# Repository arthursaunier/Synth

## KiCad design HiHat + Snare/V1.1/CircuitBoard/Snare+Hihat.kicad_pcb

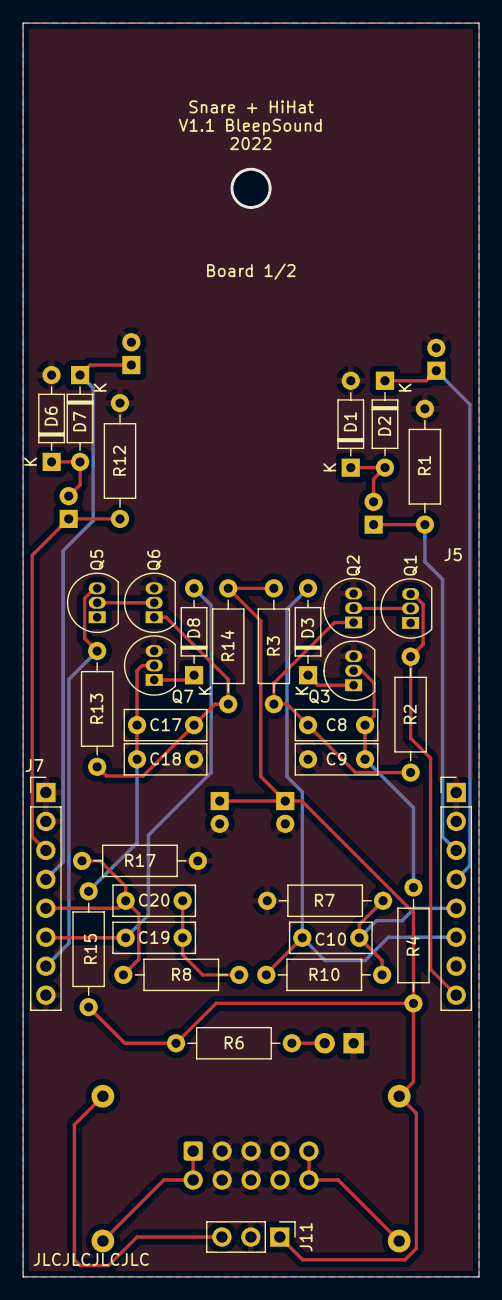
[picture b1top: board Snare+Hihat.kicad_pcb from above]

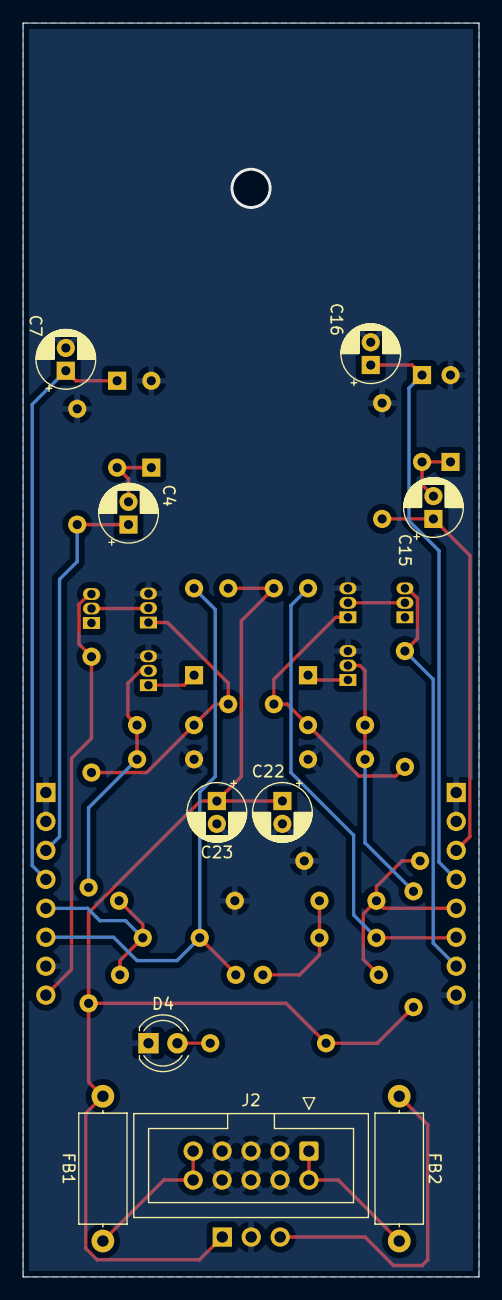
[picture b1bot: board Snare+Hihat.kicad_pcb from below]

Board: 2 copper layers, 40.0 x 110.0 mm, 45 parts (10 on the bottom side), 27 nets.

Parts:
C4, C7, C15, C16: 10µF; CP_Radial_D5.0mm_P2.00mm
C8, C17: 1µF; C_Disc_D7.0mm_W2.5mm_P5.00mm
C9: 0.1µF; C_Disc_D7.0mm_W2.5mm_P5.00mm
C10, C20: .1µF; C_Disc_D7.0mm_W2.5mm_P5.00mm
C18: 10nF; C_Disc_D7.0mm_W2.5mm_P5.00mm
C19: 680pF; C_Disc_D7.0mm_W2.5mm_P5.00mm
C22, C23: 100µ; CP_Radial_D5.0mm_P2.00mm
D1, D2, D3, D6, D7, D8: 1N4148; D_DO-35_SOD27_P7.62mm_Horizontal
D4: LED-12V; LED_D4.0mm
FB1, FB2: 10R; L_Axial_L9.5mm_D4.0mm_P12.70mm_Horizontal_Fastron_SMCC
J2: Power Input; IDC-Header_2x05_P2.54mm_Vertical
J5, J7: Conn_01x08_Male; PinHeader_1x08_P2.54mm_Vertical
J11: Conn_01x03_Male; PinHeader_1x03_P2.54mm_Vertical
Q1, Q2, Q3, Q5, Q6, Q7: BC546; TO-92_Inline
R1, R3, R12, R14: 4k7; R_Axial_DIN0207_L6.3mm_D2.5mm_P10.16mm_Horizontal
R2, R13: 47k; R_Axial_DIN0207_L6.3mm_D2.5mm_P10.16mm_Horizontal
R4, R7, R15, R17: 1M; R_Axial_DIN0207_L6.3mm_D2.5mm_P10.16mm_Horizontal
R6: 2.2k; R_Axial_DIN0207_L6.3mm_D2.5mm_P10.16mm_Horizontal
R8, R10: 0R; R_Axial_DIN0207_L6.3mm_D2.5mm_P10.16mm_Horizontal

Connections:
+12V: C22.1, C23.1, FB1.1, J11.1, R3.1, R4.1, R6.1, R14.1, R15.1
-12V: FB2.1, J11.3
/DeH: J5.8, Q1.3 (E), R2.1
/HiDH: J7.7, Q5.3 (E), R13.1
/HiH: C16.1, D7.1 (K), J7.4
/HiI: C15.1, J7.3, R12.1
/HiO: C20.2, J7.5, R8.1, R17.1
/Ho: C19.1, D8.2 (A), J7.6
/SnH: C7.1, D2.1 (K), J5.4
/SnI: C4.1, J5.3, R1.1
/SnO: C10.2, J5.5, R7.1, R10.1
/So: C10.1, D3.2 (A), J5.6, R10.2
GND: C7.2, C9.1, C16.2, C18.1, C22.2, C23.2, D1.2 (A), D4.1 (K), D6.2 (A), J2.3, J2.4, J2.5, J2.6, J2.7, J2.8, J5.1, J5.2, J5.7, J7.1, J7.2, J7.8, J11.2, Q2.3 (E), Q3.3 (E), Q6.3 (E), Q7.3 (E), R1.2, R7.2, R12.2, R17.2
unnamed: C4.2, D1.1 (K), D2.2 (A)
unnamed: C8.1, Q2.1 (C), R2.2, R3.2
unnamed: C8.2, C9.2, Q3.2 (B), R4.2
unnamed: C15.2, D6.1 (K), D7.2 (A)
unnamed: C17.1, Q6.1 (C), R13.2, R14.2
unnamed: C17.2, C18.2, Q7.2 (B), R15.2
unnamed: C19.2, C20.1, R8.2
unnamed: D3.1 (K), Q3.1 (C)
unnamed: D4.2 (A), R6.2
unnamed: D8.1 (K), Q7.1 (C)
unnamed: FB1.2, J2.9, J2.10
unnamed: FB2.2, J2.1, J2.2
unnamed: Q1.2 (B), Q2.2 (B)
unnamed: Q5.2 (B), Q6.2 (B)

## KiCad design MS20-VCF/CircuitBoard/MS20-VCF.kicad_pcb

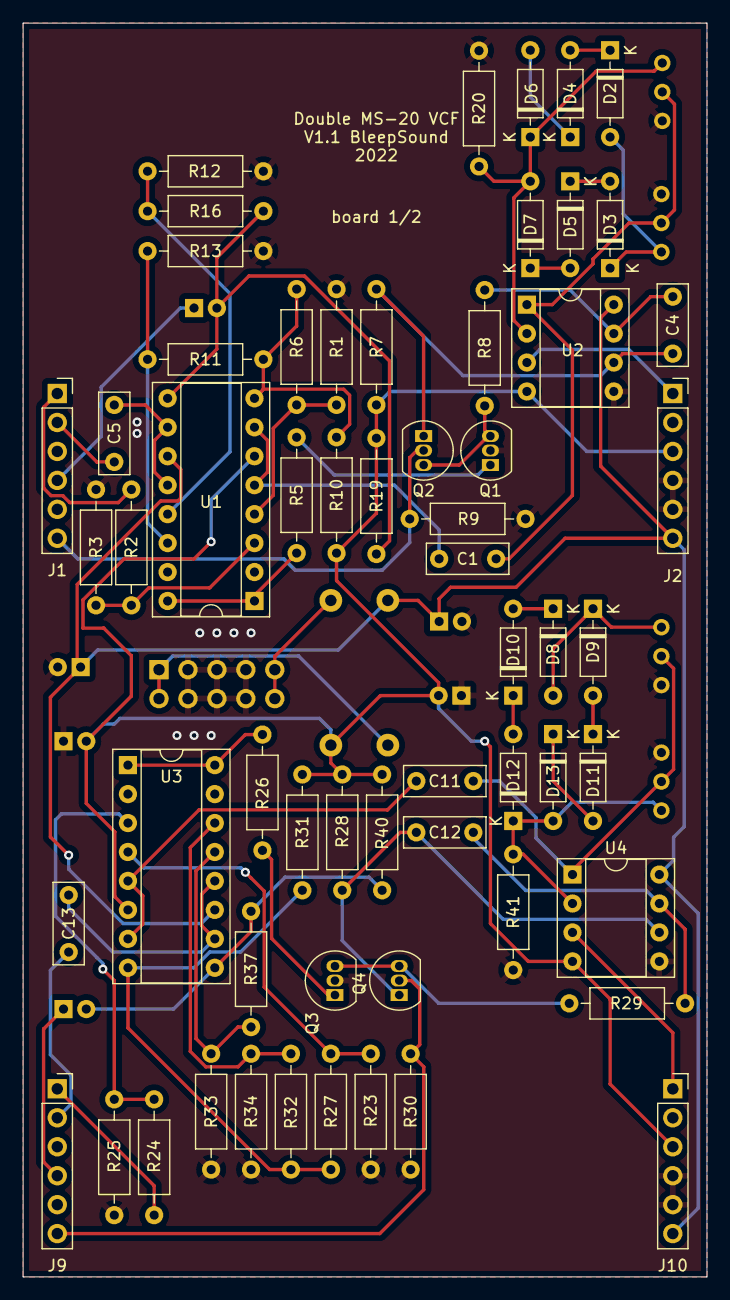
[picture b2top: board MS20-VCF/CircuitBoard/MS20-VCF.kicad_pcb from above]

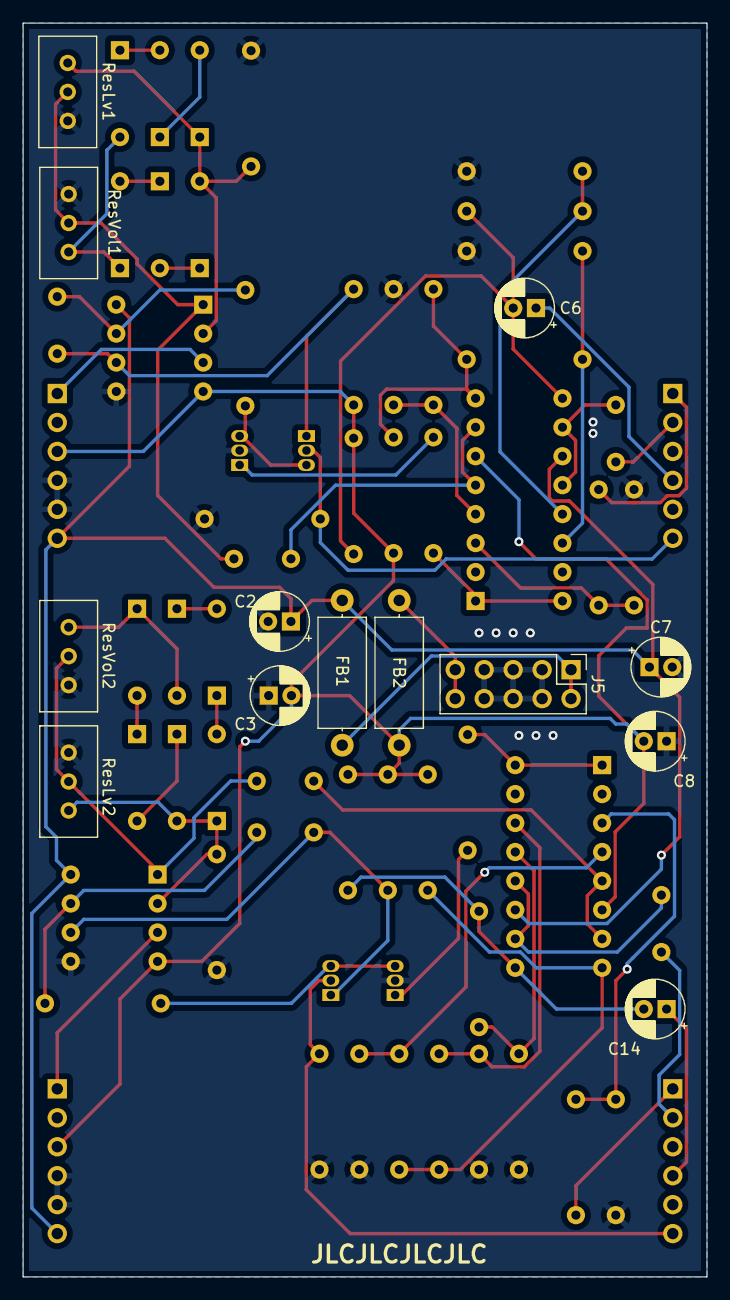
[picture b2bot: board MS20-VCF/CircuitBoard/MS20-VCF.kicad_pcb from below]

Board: 2 copper layers, 60.0 x 110.0 mm, 73 parts (13 on the bottom side), 55 nets.

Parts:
C1, C4, C5, C11, C12, C13: 1nF; C_Disc_D7.0mm_W2.5mm_P5.00mm
C2, C3: 10µ; CP_Radial_D5.0mm_P2.00mm
C6, C14: 10µF; CP_Radial_D5.0mm_P2.00mm
C7, C8: 0.1µ; CP_Radial_D5.0mm_P2.00mm
D2, D3, D4, D5, D6, D7, D8, D9, D10, D11, D12, D13: 1N4148; D_DO-35_SOD27_P7.62mm_Horizontal
FB1, FB2: 10R; L_Axial_L9.5mm_D4.0mm_P12.70mm_Horizontal_Fastron_SMCC
J1, J2, J9, J10: Conn_CircuitBoard; PinSocket_1x06_P2.54mm_Vertical
J5: Power Input; PinHeader_2x05_P2.54mm_Vertical
Q1, Q2, Q3, Q4: BC559; TO-92_Inline
R1, R3, R12, R13, R23, R25, R33, R34: 470; R_Axial_DIN0207_L6.3mm_D2.5mm_P10.16mm_Horizontal
R2, R6, R7, R11, R16, R24, R27, R28, R32, R37: 100k; R_Axial_DIN0207_L6.3mm_D2.5mm_P10.16mm_Horizontal
R5, R9, R20, R26, R30, R41: 2.2k; R_Axial_DIN0207_L6.3mm_D2.5mm_P10.16mm_Horizontal
R8, R29: 1k; R_Axial_DIN0207_L6.3mm_D2.5mm_P10.16mm_Horizontal
R10, R19, R31, R40: 1.8k; R_Axial_DIN0207_L6.3mm_D2.5mm_P10.16mm_Horizontal
ResLv1, ResLv2: 3.3k; Potentiometer_Bourns_3386C_Horizontal
ResVol1, ResVol2: 10k; Potentiometer_Bourns_3386C_Horizontal
U1, U3: LM13700; DIP-16_W7.62mm_Socket
U2, U4: TL072; DIP-8_W7.62mm_Socket

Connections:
+12V: C2.1, C7.1, FB1.1, J2.6, J10.6, U1.11 (V+), U2.8 (V+), U3.11 (V+), U4.8 (V+)
-12V: C3.2, C8.2, FB2.1, J2.3, J10.3, R7.1, R10.1, R19.1, R28.1, R31.1, R40.1, U1.6 (V-), U2.4 (V-), U3.6 (V-), U4.4 (V-)
/Cutoff: J1.6, Q2.2 (B), R9.2
/Filtre2/Cutoff: J9.6, Q4.2 (B), R30.2
/Filtre2/HPass: C13.2, J9.2
/Filtre2/LPass: J9.1, R24.1
/Filtre2/Out1: C14.1, J9.4
/Filtre2/ResOut: J10.1, U4.3 (+)
/HPass: C5.2, J1.2
/LPass: J1.1, R2.1
/Out1: C6.1, J1.4
/ResOut: J2.1, U2.3 (+)
GND: C2.2, C3.1, C7.2, C8.1, J2.4, J2.5, J5.3, J5.4, J5.5, J5.6, J5.7, J5.8, J10.4, J10.5, Q1.2 (B), Q3.2 (B), R1.1, R3.1, R9.1, R12.1, R13.1, R20.1, R23.1, R25.1, R30.1, R33.1, R34.1, R41.1, ResLv1.1, ResLv2.1, ResVol1.3, ResVol2.3, U2.5 (+), U4.5 (+)
unnamed: C1.1, U1.5, U1.7
unnamed: C1.2, ResLv1.2, ResVol1.2, U2.1
unnamed: C4.1, R8.2, U2.7
unnamed: C4.2, Q2.1 (C), R7.2, U2.6 (-)
unnamed: C5.1, U1.10, U1.12
unnamed: C6.2, R16.2, R19.2, U1.9
unnamed: C11.1, U3.5, U3.7
unnamed: C11.2, ResLv2.2, ResVol2.2, U4.1
unnamed: C12.1, R29.2, U4.7
unnamed: C12.2, Q4.1 (C), R28.2, U4.6 (-)
unnamed: C13.1, U3.10, U3.12
unnamed: C14.2, R37.2, R40.2, U3.9
unnamed: D2.1 (K), D4.2 (A)
unnamed: D2.2 (A), D3.1 (K), ResVol1.1
unnamed: D3.2 (A), D5.1 (K)
unnamed: D4.1 (K), D6.2 (A)
unnamed: D5.2 (A), D7.1 (K)
unnamed: D6.1 (K), D7.2 (A), R20.2, ResLv1.3, U2.2 (-)
unnamed: D8.2 (A), D9.1 (K), ResVol2.1
unnamed: D10.1 (K), D12.2 (A)
unnamed: D8.1 (K), D10.2 (A)
unnamed: D9.2 (A), D11.1 (K)
unnamed: D11.2 (A), D13.1 (K)
unnamed: D12.1 (K), D13.2 (A), R41.2, ResLv2.3, U4.2 (-)
unnamed: FB1.2, J5.1, J5.2
unnamed: FB2.2, J5.9, J5.10
unnamed: Q1.1 (C), R5.1
unnamed: Q1.3 (E), Q2.3 (E), R8.1
unnamed: Q3.1 (C), R26.1
unnamed: Q3.3 (E), Q4.3 (E), R29.1
unnamed: R1.2, R6.1, U1.4 (-)
unnamed: R2.2, R3.2, U1.3 (+)
unnamed: R5.2, U1.1, U1.16
unnamed: R6.2, R10.2, R11.1, U1.8
unnamed: R11.2, R13.2, U1.14 (+)
unnamed: R12.2, R16.1, U1.13 (-)
unnamed: R23.2, R27.1, U3.4 (-)
unnamed: R24.2, R25.2, U3.3 (+)
unnamed: R26.2, U3.1, U3.16
unnamed: R27.2, R31.2, R32.1, U3.8
unnamed: R32.2, R34.2, U3.14 (+)
unnamed: R33.2, R37.1, U3.13 (-)

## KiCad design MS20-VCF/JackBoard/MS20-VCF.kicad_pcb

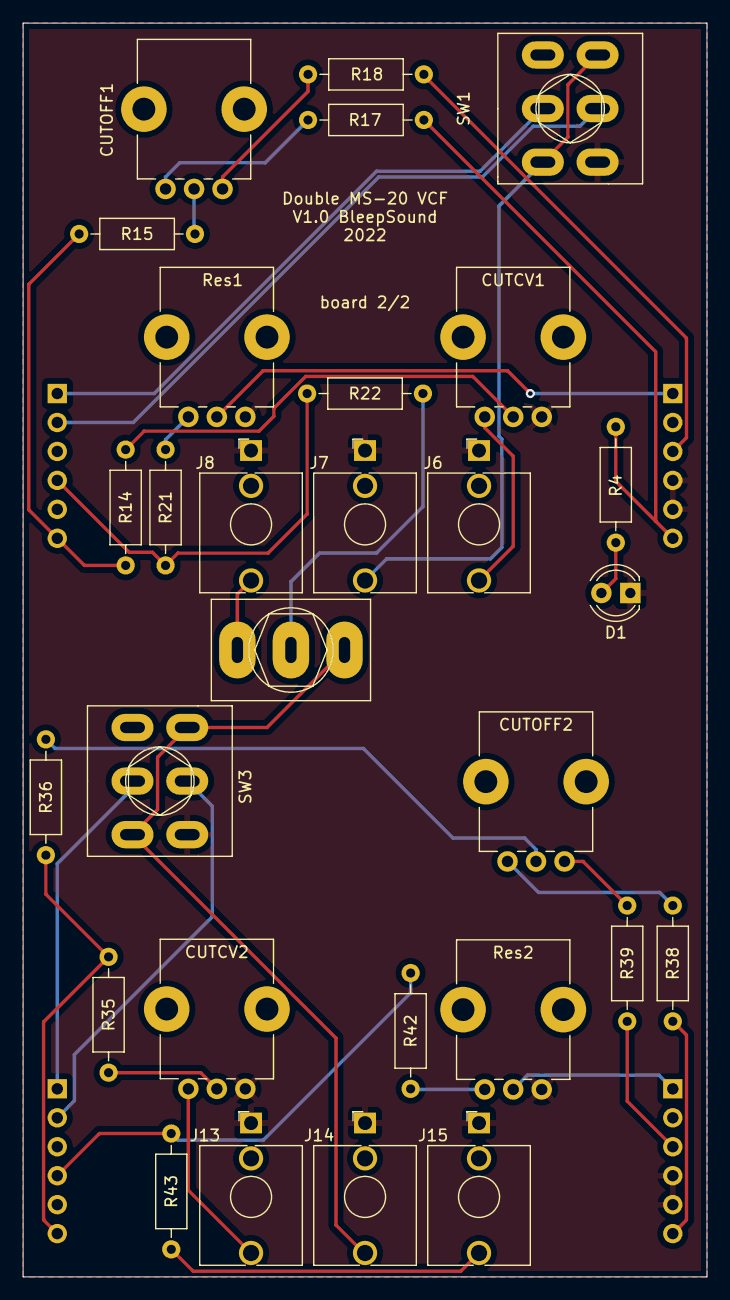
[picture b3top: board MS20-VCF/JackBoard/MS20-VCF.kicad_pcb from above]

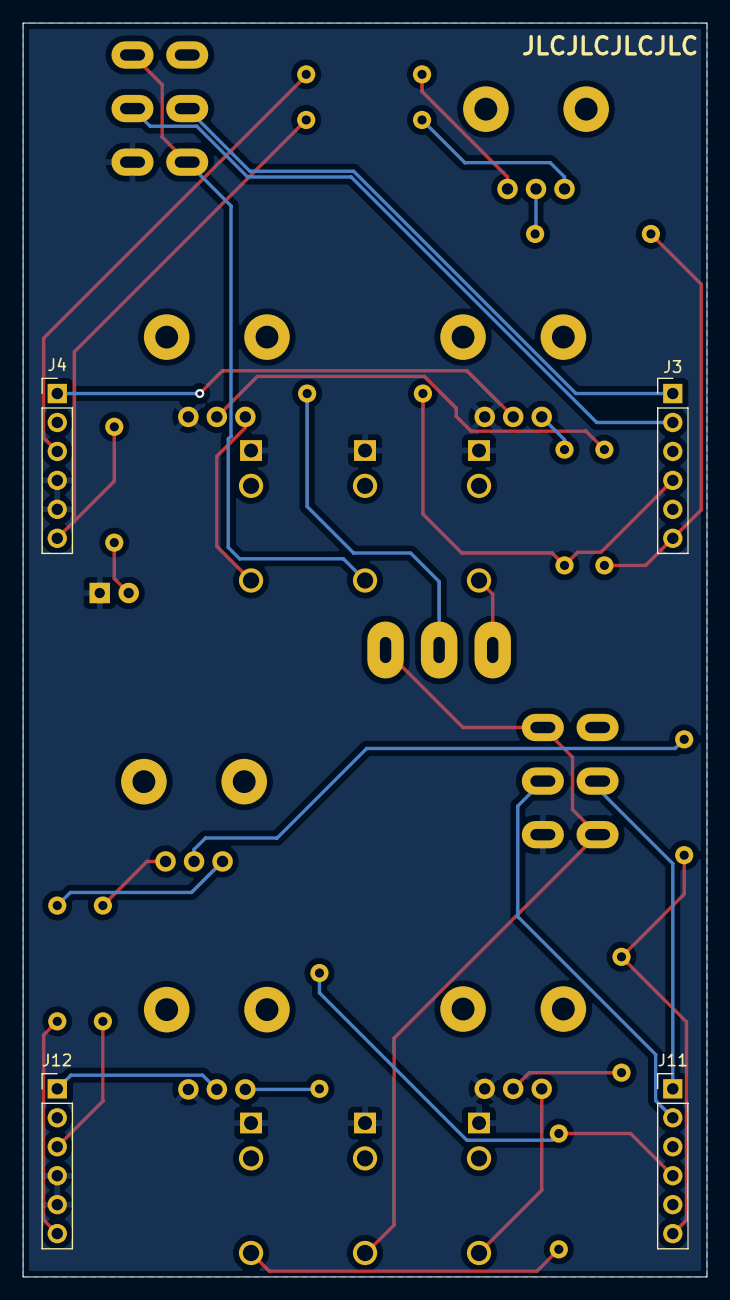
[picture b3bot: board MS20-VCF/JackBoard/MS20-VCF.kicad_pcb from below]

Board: 2 copper layers, 60.0 x 110.0 mm, 33 parts (4 on the bottom side), 31 nets.

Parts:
CUTCV1, CUTCV2: 100k; Potentiometer_Bourns_PTV09A-1_Single_Vertical
CUTOFF1, CUTOFF2: 100k; Potentiometer_Bourns_PTV09A-1_Single_Vertical
D1: LED-12V; LED_D4.0mm
J3, J4, J11, J12: Conn_JackBoard; PinHeader_1x06_P2.54mm_Vertical
J6: FilterCV1; Jack_3.5mm_QingPu_WQP-PJ398SM_Vertical_CircularHoles
J7: FilterIn1; Jack_3.5mm_QingPu_WQP-PJ398SM_Vertical_CircularHoles
J8: FilterOut1; Jack_3.5mm_QingPu_WQP-PJ398SM_Vertical_CircularHoles
J13: FilterCV2; Jack_3.5mm_QingPu_WQP-PJ398SM_Vertical_CircularHoles
J14: FilterIn2; Jack_3.5mm_QingPu_WQP-PJ398SM_Vertical_CircularHoles
J15: FilterOut2; Jack_3.5mm_QingPu_WQP-PJ398SM_Vertical_CircularHoles
R4: 2.2k; R_Axial_DIN0207_L6.3mm_D2.5mm_P10.16mm_Horizontal
R14, R35: 82k; R_Axial_DIN0207_L6.3mm_D2.5mm_P10.16mm_Horizontal
R15, R36: 100k; R_Axial_DIN0207_L6.3mm_D2.5mm_P10.16mm_Horizontal
R17, R38: 33k; R_Axial_DIN0207_L6.3mm_D2.5mm_P10.16mm_Horizontal
R18, R39: 56k; R_Axial_DIN0207_L6.3mm_D2.5mm_P10.16mm_Horizontal
R21, R22, R42, R43: 1k; R_Axial_DIN0207_L6.3mm_D2.5mm_P10.16mm_Horizontal
Res1, Res2: 100k; Potentiometer_Bourns_PTV09A-1_Single_Vertical
SW1, SW3: Hpass/Lpass Switch; SW_DPDT_Toggle
SW2: Bandpass; SW_Toggle_Blue_wSlots

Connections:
+12V: J4.6, J12.6, R4.1, R17.2, R38.2
-12V: J4.3, J12.3, R18.1, R39.1
/CVIn: CUTCV1.3, J6.T
/Cutoff: J3.6, R14.1, R15.1
/FilterIn: J7.T, SW1.3 (C), SW1.4 (A)
/FilterOut: R22.1, SW2.2 (B)
/Filtre2/CVIn: CUTCV2.3, J13.T
/Filtre2/Cutoff: J11.6, R35.1, R36.1
/Filtre2/FilterOut: J15.T, R43.1
/Filtre2/HPass: J11.2, SW3.5 (B)
/Filtre2/LPass: J11.1, SW3.2 (B)
/Filtre2/Out1: J11.4, R42.2, R43.2
/Filtre2/ResOut: J12.1, Res2.2
/HPass: J3.2, SW1.5 (B)
/JackOut: J8.T, SW2.1 (A)
/LPass: J3.1, SW1.2 (B)
/Out1: J3.4, R21.2, R22.2
/ResOut: J4.1, Res1.2
Filter2In: J14.T, SW2.3 (C), SW3.3 (C), SW3.4 (A)
GND: CUTCV1.1, CUTCV2.1, D1.1 (K), J4.4, J4.5, J6.S, J7.S, J8.S, J12.4, J12.5, J13.S, J14.S, J15.S, Res1.1, Res2.1, SW1.6 (C), SW3.6 (C)
unnamed: CUTCV1.2, R14.2
unnamed: CUTCV2.2, R35.2
unnamed: CUTOFF1.1, R18.2
unnamed: CUTOFF1.2, R15.2
unnamed: CUTOFF1.3, R17.1
unnamed: CUTOFF2.1, R39.2
unnamed: CUTOFF2.2, R36.2
unnamed: CUTOFF2.3, R38.1
unnamed: D1.2 (A), R4.2
unnamed: R21.1, Res1.3
unnamed: R42.1, Res2.3
